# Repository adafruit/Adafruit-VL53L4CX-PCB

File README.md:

## Adafruit VL53L4CX Time of Flight Distance Sensor PCB

<a href="http://www.adafruit.com/products/5425"><br/>
Click here to purchase one from the Adafruit shop</a>

PCB files for the Adafruit VL53L4CX Time of Flight Distance Sensor. 

Format is EagleCAD schematic and board layout
* https://www.adafruit.com/product/5425

### Description

The Adafruit VL53L4CX Time of Flight Sensor is another great Time of Flight distance sensor from ST in the VL5 series of chips, this one is great for long distances - it goes up to 6 meters compared with 4 meter max of the VL53L1X.

The sensor contains a very tiny invisible laser source and a matching sensor. The VL53L4CX can detect the "time of flight", or how long the light has taken to bounce back to the sensor. Since it uses a very narrow light source, it is good for determining distance of only the surface directly in front of it. Unlike sonars that bounce ultrasonic waves, the 'cone' of sensing is very narrow. Unlike IR distance sensors that try to measure the amount of light bounced, the VL53 is much more precise and doesn't have linearity problems or 'double imaging' where you can't tell if an object is very far or very close.

This is a 'big sister' of the VL53L4CD ToF sensor and can handle about ~1 to 6000mm of range distance, it also has some ability to do 'multi object detection'. Basically it can identify when more than one object is in view and tell you the two distances.

Please note, the Arduino driver for this chip does not support 'small memory' boards like the ATmega328 - you'll need a SAMD21, SAMD51, ESP, etc chip with 50K of flash memory available!

The sensor is small and easy to use in any robotics or interactive project. Since it needs 2.8V power and logic we put the little fellow on a breakout board with a regulator and level shifting. You can use it with any 3-5V power or logic microcontroller with no worries. Works great with the 3.3V logic level of a Feather, or the 5v level of a Arduino Mega, this breakout is ready to work with most common microcontrollers or SBCs. and since it speaks I2C, you can easily connect it up with two data wires plus power and ground. 

As if that weren't enough, we've also added SparkFun qwiic compatible STEMMA QT connectors for the I2C bus so you don't even need to solder. Just wire up to your favorite micro with a plug-and-play cable to get ToF data ASAP. For a no-solder experience, just wire up to your favorite micro, like the STM32F405 Feather using a STEMMA QT adapter cable. The Stemma QT connectors also mean the VL53L4CX can be used with our various associated accessories. QT Cable is not included, but we have a variety in the shop

Communicating to the sensor is done over I2C with an API written by ST, they have an Arduino library with an example for communication

### License

Adafruit invests time and resources providing this open source design, please support Adafruit and open-source hardware by purchasing products from [Adafruit](https://www.adafruit.com)!

Designed by Limor Fried/Ladyada for Adafruit Industries.

Creative Commons Attribution/Share-Alike, all text above must be included in any redistribution. 
See license.txt for additional details.

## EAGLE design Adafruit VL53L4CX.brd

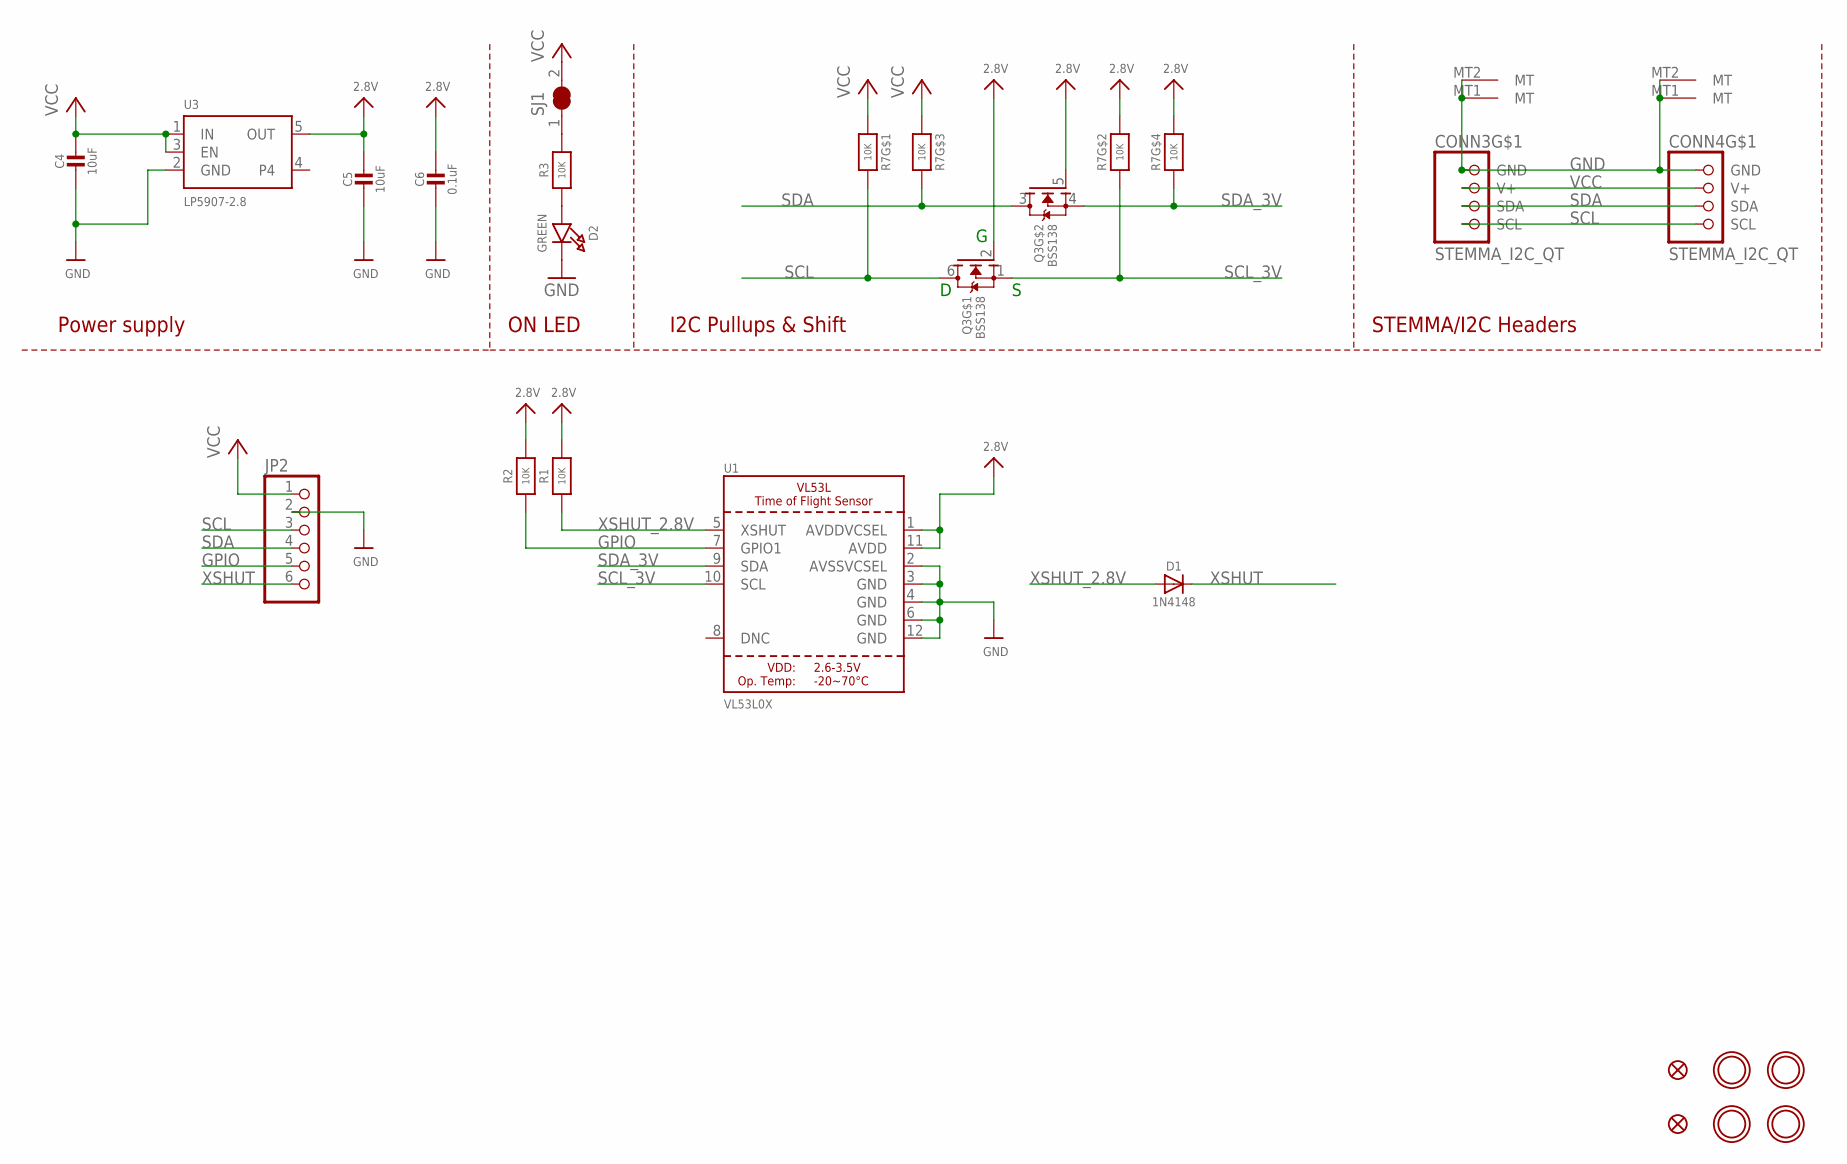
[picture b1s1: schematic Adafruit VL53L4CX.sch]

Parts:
C4, C5: 10uF; 0805-NO
C6: 0.1uF; 0603-NO
CONN3, CONN4: STEMMA_I2C_QT; JST_SH4
D1: 1N4148; SOD-323
D2: GREEN; CHIPLED_0603_NOOUTLINE
FID1, FID4: FIDUCIAL_1MM
JP2: HEADER-1X670MIL; 1X06_ROUND_70
Q3: BSS138; SOT363
R1, R2, R3: 10K; 0603-NO
R7: 10K; RESPACK_4X0603
SJ1: SOLDERJUMPER_CLOSED; SOLDERJUMPER_CLOSEDWIRE
U1: VL53L0X; LGA12_ST
U3: LP5907-2.8; SOT23-5
U$30, U$31, U$33, U$34: MOUNTINGHOLE2.5; MOUNTINGHOLE_2.5_PLATED

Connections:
2.8V: C5.1, C6.1, Q3.2 (G), Q3.5 (G), R1.2, R2.2, R7.2 (1), R7.4 (1), U1.1 (AVDDVCSEL), U1.11 (AVDD), U3.5 (OUT)
GND: C4.2, C5.2, C6.2, CONN3.1 (GND), CONN3.MT1 (MT), CONN3.MT2 (MT), CONN4.1 (GND), CONN4.MT1 (MT), CONN4.MT2 (MT), D2.C, JP2.2, U1.2 (AVSSVCSEL), U1.3 (GND), U1.4 (GND), U1.6 (GND), U1.12 (GND), U3.2 (GND)
GPIO: JP2.5, R2.1, U1.7 (GPIO1)
unnamed: D2.A, R3.1
unnamed: R3.2, SJ1.1
SCL: CONN3.4 (SCL), CONN4.4 (SCL), JP2.3, Q3.6 (D), R7.8 (2)
SCL_3V: Q3.1 (S), R7.7 (2), U1.10 (SCL)
SDA: CONN3.3 (SDA), CONN4.3 (SDA), JP2.4, Q3.3 (D), R7.6 (2)
SDA_3V: Q3.4 (S), R7.5 (2), U1.9 (SDA)
VCC: C4.1, CONN3.2 (V+), CONN4.2 (V+), JP2.1, R7.1, R7.3 (1), SJ1.2, U3.1 (IN), U3.3 (EN)
XSHUT: D1.C, JP2.6
XSHUT_2.8V: D1.A, R1.1, U1.5 (XSHUT)

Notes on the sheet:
I2C Pullups & Shift
STEMMA/I2C Headers
ON LED
Power supply

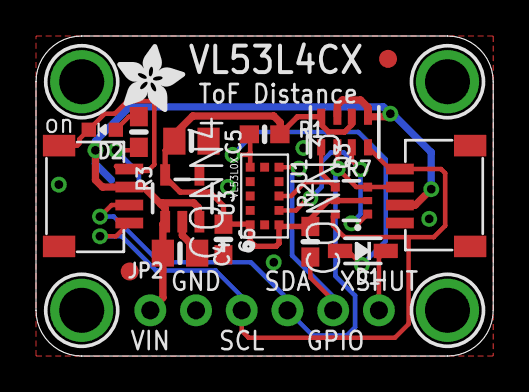
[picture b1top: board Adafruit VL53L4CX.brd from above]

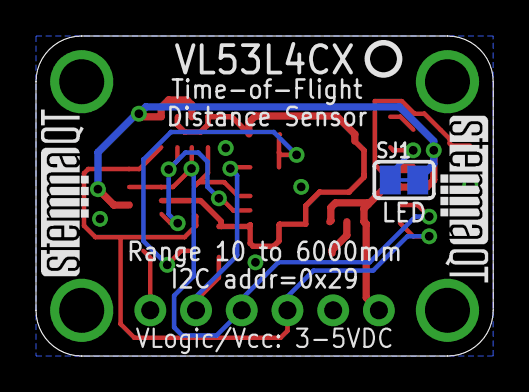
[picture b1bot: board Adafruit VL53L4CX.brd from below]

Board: 2 copper layers, 25.4 x 17.8 mm, 26 parts (4 on the bottom side), 12 nets.

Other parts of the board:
U$36: ADAFRUIT_3.5MM
U$37: PCBFEAT-REV-040
U$38, U$39: STEMMAQT

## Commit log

2022-04-29 Adding files from cookiecutter run
    Adding readme, board files, product image

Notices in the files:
parts and their libraries:
microbuilder: This work is placed in the public domain, and may be freely used for commercial and non-commercial work with the following conditions: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
